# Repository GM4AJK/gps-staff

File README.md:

# GPS Survey Staff

A DIY RTK GNSS survey staff -- a handheld device for centimetre-level accurate position surveying.

## What is this?

The system consists of two identical handheld units: one set up as a fixed base station, the other carried by the surveyor as a rover. The two communicate wirelessly so the rover can compute corrected, centimetre-accurate positions in real time (RTK -- Real-Time Kinematic positioning).

It's designed to be self-contained and portable -- battery powered, with an onboard display, simple button/encoder controls, and onboard logging of survey data for later processing.

## Project status

Active development. PCB v1.0 ordered 2026-06-25. Firmware bring-up ongoing on Nucleo dev boards.

## Documentation

| Location | Contents |
|----------|----------|
| [`sdd/`](sdd/) | System design: architecture, unit specs, BLE protocols, UI screen specs |
| [`docs/arch/`](docs/arch/) | Firmware architecture: RTCM3, OTA protocol, SX1262 driver, SD card |
| [`docs/datasheets/`](docs/datasheets/) | Component datasheets and reference documents |
| [`hardware/rtk/`](hardware/rtk/) | PCB electronics design: KiCad files, BOM, design notes |

## License

MIT — see [LICENSE](LICENSE). This project is provided for educational and personal use without warranty of any kind. No liability is accepted for any use of these designs, including use in safety-critical or commercial applications. Use at your own risk.

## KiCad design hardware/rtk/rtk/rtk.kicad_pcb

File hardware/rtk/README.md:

# RTK PCB — Electronics Design

## PCB v1.0

- **Ordered:** 2026-06-25, JLCPCB. Tagged `PCB-v1.0` in git.
- **DigiKey BOM** ordered same date.
- **KiCad files:** `hardware/rtk/rtk/`
- **Component BOM:** [BOM.md](BOM.md)

### Board overview

| Property | Value |
|----------|-------|
| Layers | 4 (JLC04161H-7628 stackup) |
| Layer assignment | L1 top signal + components; L2 solid GND; L3 3.3V power plane; L4 bottom signal |
| RF traces | 50Ω microstrip on L1 (L2 GND reference); ~0.7mm trace width; JLCPCB controlled impedance |
| Design | Unified base + rover — single PCB, role selected by jumper at boot |
| Role-specific DNP | USB-C #1 (base: OTG FS) vs USB-C #2 + ULPI PHY (rover: OTG HS) |

### Unified PCB approach

Both units built from the same PCB. Mode selection:
- `PA0` (BASE_ROVER_MODE_SELECT): internal pull-up, link open = base, link to GND = rover
- Same STM32 firmware binary on both; mode gates peripheral init and code paths at runtime
- ESP32-S3 Zero firmware differs per role (base: WiFi NTRIP + BLE prov; rover: BLE GATT server)

---

## Schematic Connection Checklist

Consolidated list of every system wired on the schematic. Reference against the BOM and KiCad
to verify nothing is missed.

1. **ZED-F9P-05B** — UART1 (pins 42/43) → STM32 UART5 (nav + UBX config); UART2 (pins 26/27)
   → STM32 UART7 (PA8 RX ← F9P TXD2, PA15 TX → F9P RXD2) for RTCM input from LoRa;
   D_SEL (pin 47) → PE14 high (UART/I2C mode); RF_IN → GNSS SMA via 50Ω trace;
   1PPS → STM32 GPIO (log timestamping); power + decoupling.

2. **GNSS antenna (ANN-MB-00)** — SMA female through-hole; bias-T 3.3V LNA feed on RF line.

3. **LoRa (Core1262-LF / SX1262)** — dedicated SPI bus; BUSY checked before every transaction;
   DIO1/IRQ → STM32 GPIO; NRESET; separate SMA (433/434MHz).

4. **STM32F765VIT6** — UART (F9P + spare); 2× dedicated SPI (LoRa, IMU); SDMMC1 4-bit
   (PC8/D0, PC9/D1, PC10/D2, PC11/D3, PC12/CLK, PD2/CMD — fixed AF pins);
   I2C4 (PD12 SCL, PD13 SDA — display + IMU); USB OTG FS (PA11/PA12, base) or
   OTG HS + ULPI (rover); ADC (battery divider PA1); SWD.

5. **Power chain** — TPS63020 with D1 + C_SS soft-start on FB node; BQ24075 power-path
   (EN1/EN2/SYSOFF/nCE → STM32 GPIO outputs; nPGOOD/nCHG → STM32 GPIO inputs; TS → 10K to GND);
   LP103454-PCM-LD 2-wire battery connector (J3); 100K/100K battery voltage divider → PA1 ADC.

6. **USB-C (J1)** — single connector footprint, routed via USB3300 ULPI PHY (U8) to STM32
   OTG HS; CC1/CC2 5.1K pull-downs (R11/R12); USBLC6-2SC6 ESD (D2); USB3300 RST (PC1);
   24MHz TCXO (Y2); 12K RBIAS (R9); full decoupling.
   *(Base build: USB-C #2 + ULPI PHY fitted; USB-C #1 DNP. Both are HS-capable.)*

7. **IMU (LSM6DSOX/DSRX, U7)** — I2C4 (PD12/PD13); INT1 → PD14; INT2 → PD15.
   **Magnetometer (MMC5603NJ)** — sub-board via J11 (6-pin 0.1" header, I2C4 bus).

8. **SD card (J6)** — SDMMC1 4-bit bus (fixed AF pins above); card-detect → GPIO; well-decoupled VCC.

9. **STM32 backup domain (VBAT)** — wired directly to 3.3V rail; no coin cell.

10. **Config storage** — SD card file; no EEPROM fitted.

11. **OLED display (SSD1309)** — via J7 header; I2C4 bus (PD12 SCL, PD13 SDA); 0x3C/0x3D.
    On PCB v1.0. Driver bench-verified on F767ZI (task_display.c, ssd1309.c).

12. **Status LEDs** — LD3 (PD5, green) + LD4 (PD6, red): MCU open-drain + pull-ups R20/R21;
    LD1/LD2 hardwired to BQ24075 nPGOOD/nCHG.

13. **Mode-selection jumper** — PA0 GPIO input, internal pull-up; high = base, low = rover.

14. **BOOT0** — 2-pin header, 10K pull-down to GND; fitted = DFU bootloader.

15. **ESP32-S3 Zero (U5)** — spare STM32 UART; 3.3V power + decoupling; mode-select via
    PE2 (GP1) + PE3 (GP2/MODE_VALID). Base: WiFi NTRIP + BLE prov server.
    Rover: BLE GATT server to handheld.

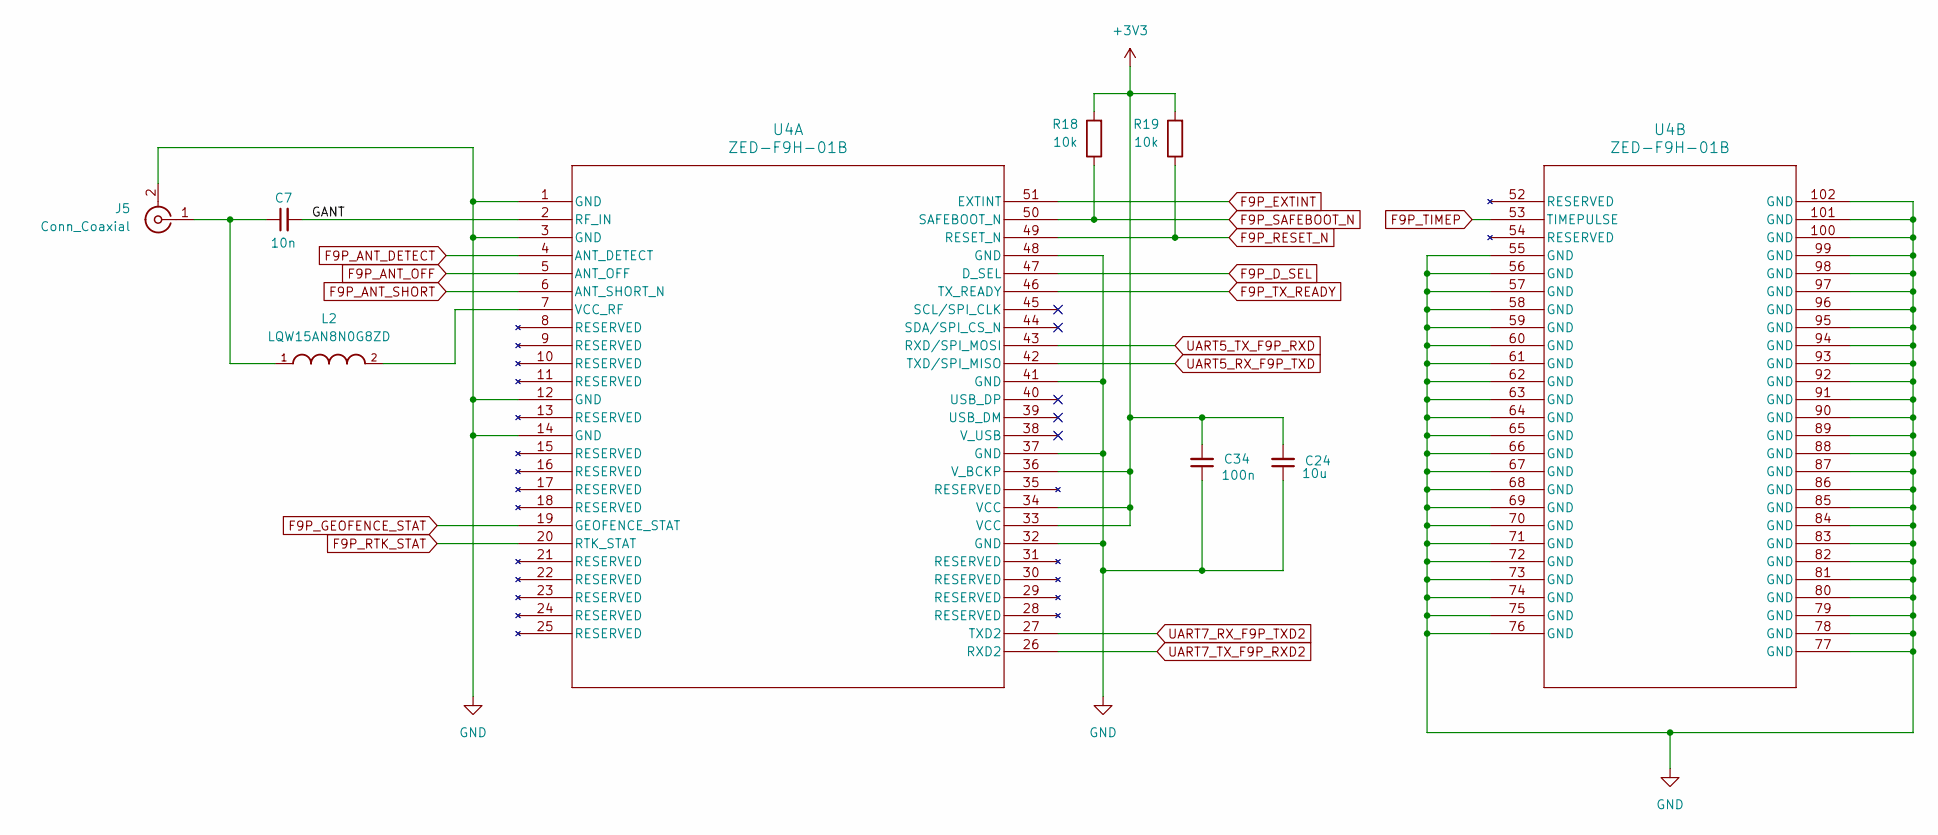
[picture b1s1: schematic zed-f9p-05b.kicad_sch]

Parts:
C7: 10n; C_0603_1608Metric_Pad1.08x0.95mm_HandSolder
C24: 10u; C_0805_2012Metric_Pad1.18x1.45mm_HandSolder
C34: 100n; C_0603_1608Metric_Pad1.08x0.95mm_HandSolder
J5: Conn_Coaxial; SMA_BAT_Wireless_BWSMA-KWE-Z001
L2: LQW15AN8N0G8ZD; INDC1006X60N
R18, R19: 10k; R_0805_2012Metric_Pad1.20x1.40mm_HandSolder
U4: ZED-F9H-01B; MOD54_ZED-F9H_UBL

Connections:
+3V3: C24.2, C34.2, R18.2, R19.2, U4.33 (VCC), U4.34 (VCC), U4.36 (V_BCKP); also elsewhere on the board
/ZED-F9P-05B/GANT: C7.2, U4.2 (RF_IN)
F9P_ANT_DETECT: U4.4 (ANT_DETECT); also elsewhere on the board
F9P_ANT_OFF: U4.5 (ANT_OFF); also elsewhere on the board
F9P_ANT_SHORT: U4.6 (ANT_SHORT_N); also elsewhere on the board
F9P_D_SEL: U4.47 (D_SEL); also elsewhere on the board
F9P_EXTINT: U4.51 (EXTINT); also elsewhere on the board
F9P_GEOFENCE_STAT: U4.19 (GEOFENCE_STAT); also elsewhere on the board
F9P_RESET_N: R19.1, U4.49 (RESET_N); also elsewhere on the board
F9P_RTK_STAT: U4.20 (RTK_STAT); also elsewhere on the board
F9P_SAFEBOOT_N: R18.1, U4.50 (SAFEBOOT_N); also elsewhere on the board
F9P_TIMEP: U4.53 (TIMEPULSE); also elsewhere on the board
F9P_TX_READY: U4.46 (TX_READY); also elsewhere on the board
GND: C24.1, C34.1, J5.2 (Ext), U4.1 (GND), U4.3 (GND), U4.12 (GND), U4.14 (GND), U4.32 (GND), U4.37 (GND), U4.41 (GND), U4.48 (GND), U4.55 (GND), U4.56 (GND), U4.57 (GND), U4.58 (GND), U4.59 (GND), U4.60 (GND), U4.61 (GND), U4.62 (GND), U4.63 (GND), U4.64 (GND), U4.65 (GND), U4.66 (GND), U4.67 (GND), U4.68 (GND), U4.69 (GND), U4.70 (GND), U4.71 (GND), U4.72 (GND), U4.73 (GND), U4.74 (GND), U4.75 (GND), U4.76 (GND), U4.77 (GND), U4.78 (GND), U4.79 (GND), U4.80 (GND), U4.81 (GND), U4.82 (GND), U4.83 (GND), U4.84 (GND), U4.85 (GND), U4.86 (GND), U4.87 (GND), U4.88 (GND), U4.89 (GND), U4.90 (GND), U4.91 (GND), U4.92 (GND), U4.93 (GND), U4.94 (GND), U4.95 (GND), U4.96 (GND), U4.97 (GND), U4.98 (GND), U4.99 (GND), U4.100 (GND), U4.101 (GND), U4.102 (GND); also elsewhere on the board
unnamed: C7.1, J5.1 (In), L2.1
unnamed: L2.2, U4.7 (VCC_RF)
UART5_RX_F9P_TXD: U4.42 (TXD/SPI_MISO); also elsewhere on the board
UART5_TX_F9P_RXD: U4.43 (RXD/SPI_MOSI); also elsewhere on the board
UART7_RX_F9P_TXD2: U4.27 (TXD2); also elsewhere on the board
UART7_TX_F9P_RXD2: U4.26 (RXD2); also elsewhere on the board

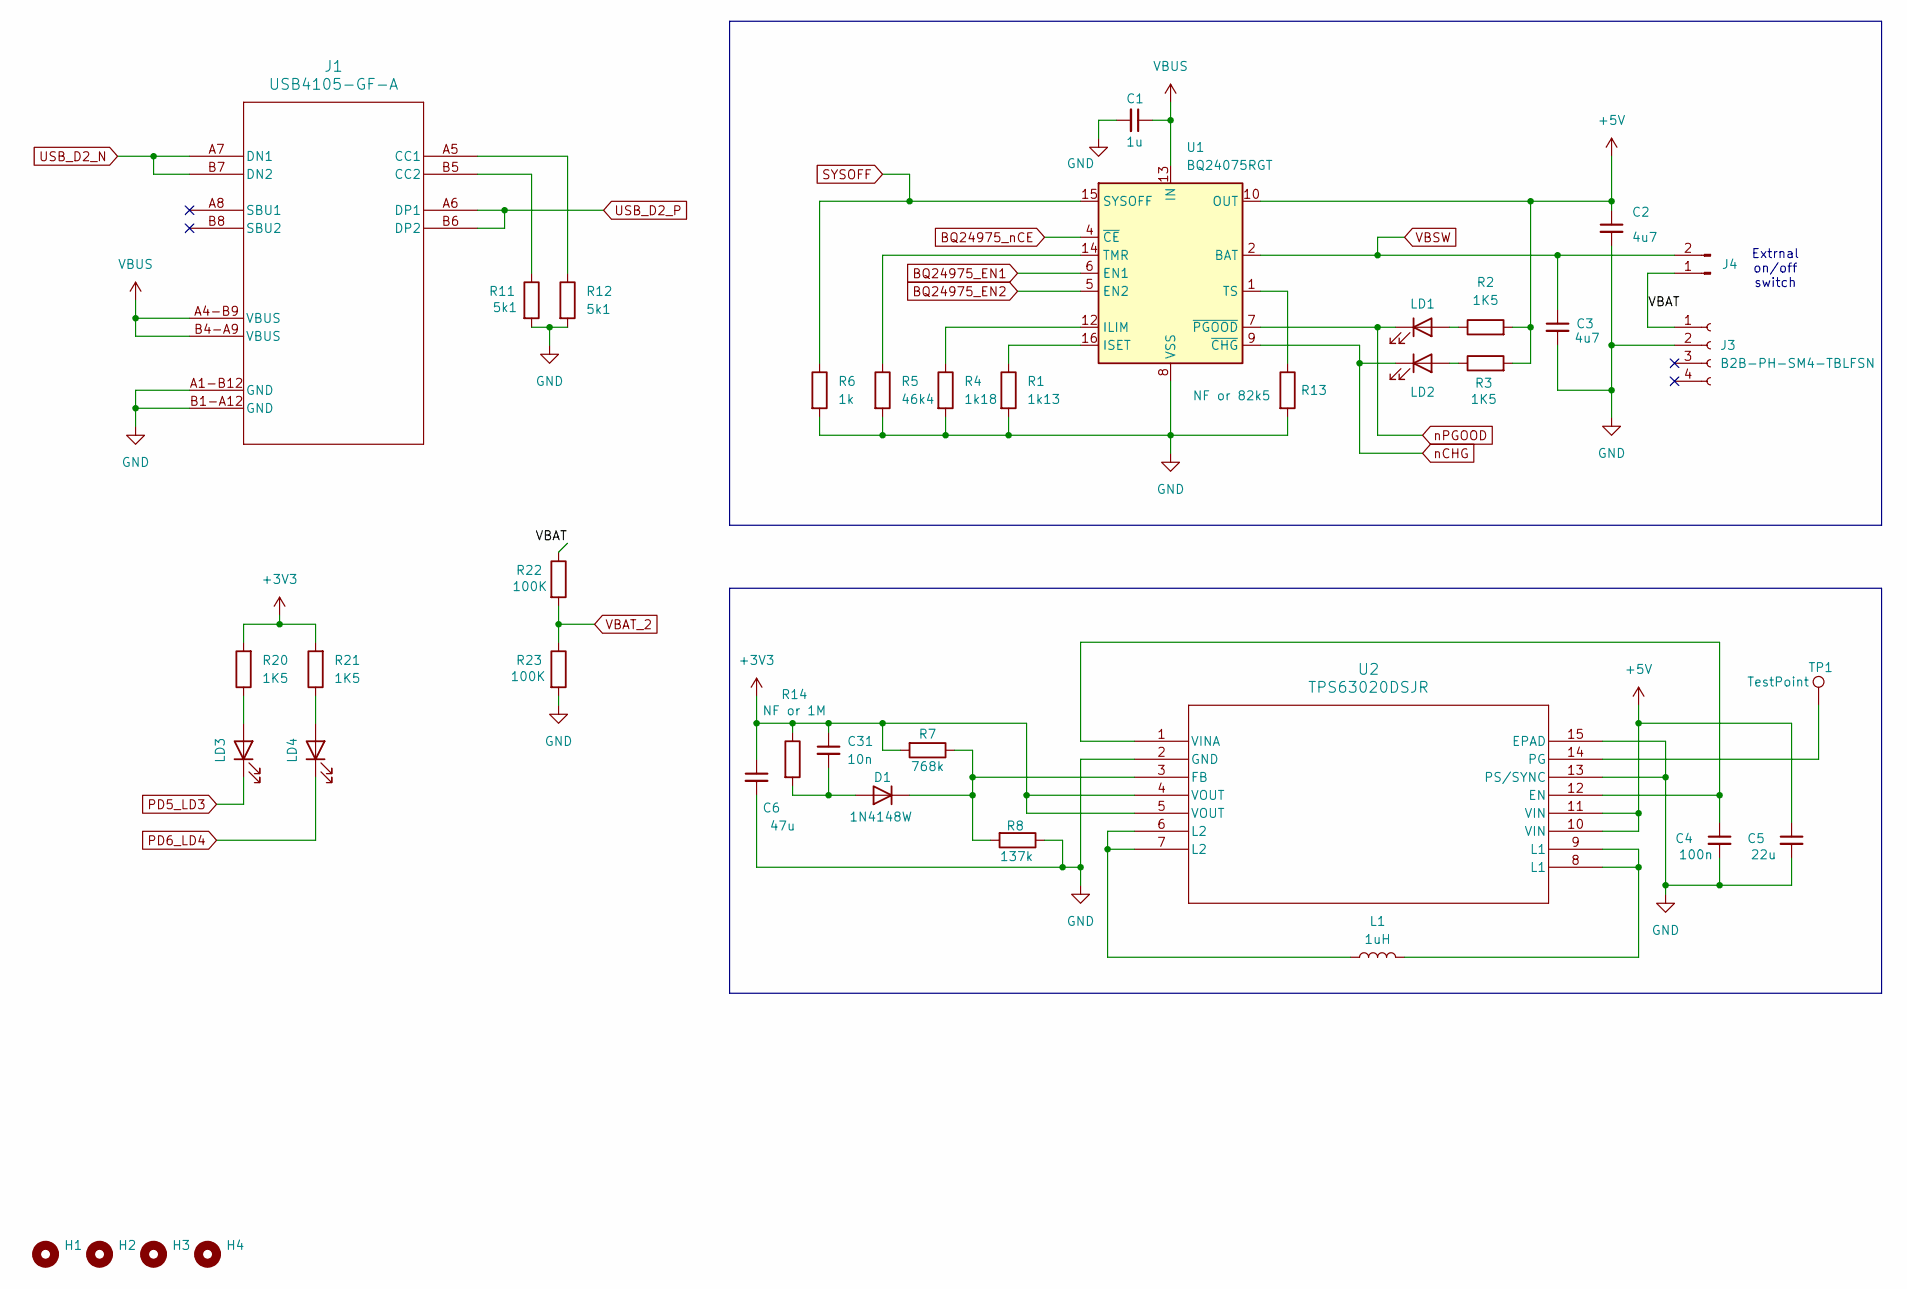
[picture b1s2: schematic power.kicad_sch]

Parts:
C1: 1u; C_0805_2012Metric_Pad1.18x1.45mm_HandSolder
C2, C3: 4u7; C_0805_2012Metric_Pad1.18x1.45mm_HandSolder
C4: 100n; C_0603_1608Metric_Pad1.08x0.95mm_HandSolder
C5: 22u; C_0603_1608Metric_Pad1.08x0.95mm_HandSolder
C6: 47u; C_0805_2012Metric_Pad1.18x1.45mm_HandSolder
C31: 10n; C_0805_2012Metric_Pad1.18x1.45mm_HandSolder
D1: 1N4148W; D_SOD-123
H1, H2, H3, H4: MountingHole; MountingHole_2.7mm
J1: USB4105-GF-A; USB4105_GCT
J3: B2B-PH-SM4-TBLFSN; CONN_B2B-PH-SM4-TBLFSN_JST
J4: Conn_01x02_Pin; PinHeader_1x02_P2.54mm_Vertical
L1: 1uH; IND_DFE2016_2X1P6_MUR
LD1, LD2, LD3, LD4: LED; LED_0805_2012Metric_Pad1.15x1.40mm_HandSolder
R1: 1k13; R_0805_2012Metric_Pad1.20x1.40mm_HandSolder
R2, R3, R20, R21: 1K5; R_0805_2012Metric_Pad1.20x1.40mm_HandSolder
R4: 1k18; R_0805_2012Metric_Pad1.20x1.40mm_HandSolder
R5: 46k4; R_0805_2012Metric_Pad1.20x1.40mm_HandSolder
R6: 1k; R_0805_2012Metric_Pad1.20x1.40mm_HandSolder
R7: 768k; R_0805_2012Metric_Pad1.20x1.40mm_HandSolder
R8: 137k; R_0805_2012Metric_Pad1.20x1.40mm_HandSolder
R11, R12: 5k1; R_0805_2012Metric_Pad1.20x1.40mm_HandSolder
R13: NF or 82k5; R_0805_2012Metric_Pad1.20x1.40mm_HandSolder
R14: NF or 1M; R_0805_2012Metric_Pad1.20x1.40mm_HandSolder
R22, R23: 100K; R_0805_2012Metric_Pad1.20x1.40mm_HandSolder
TP1: TestPoint; PinHeader_1x01_P2.54mm_Vertical
U1: BQ24075RGT; VQFN-16-1EP_3x3mm_P0.5mm_EP1.6x1.6mm
U2: TPS63020DSJR; DSJ14_2P85X1P58

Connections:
+3V3: C6.1, C31.1, R7.2, R14.1, R20.2, R21.2, U2.4 (VOUT), U2.5 (VOUT); also elsewhere on the board
+5V: C2.1, C5.1, R2.2, R3.2, U1.10 (OUT), U1.11 (OUT), U2.10 (VIN), U2.11 (VIN)
/Power/VBAT: J3.1, J4.1, R22.1
BQ24975_EN1: U1.6 (EN1); also elsewhere on the board
BQ24975_EN2: U1.5 (EN2); also elsewhere on the board
BQ24975_nCE: U1.4 (~CE); also elsewhere on the board
GND: C1.2, C2.2, C3.2, C4.2, C5.2, C6.2, J1.A1-B12 (GND), J1.B1-A12 (GND), J3.2, R1.2, R4.2, R5.2, R6.2, R8.1, R11.2, R12.2, R13.2, R23.2, U1.8 (VSS), U1.17 (VSS), U2.2 (GND), U2.13 (PS/SYNC), U2.15 (EPAD); also elsewhere on the board
unnamed: C31.2, D1.2 (A), R14.2
unnamed: D1.1 (K), R7.1, R8.2, U2.3 (FB)
unnamed: J1.A5 (CC1), R12.1
unnamed: J1.B5 (CC2), R11.1
unnamed: L1.1, U2.6 (L2), U2.7 (L2)
unnamed: L1.2, U2.8 (L1), U2.9 (L1)
unnamed: LD1.2 (A), R2.1
unnamed: LD2.2 (A), R3.1
unnamed: LD3.2 (A), R20.1
unnamed: LD4.2 (A), R21.1
unnamed: R4.1, U1.12 (ILIM)
unnamed: R1.1, U1.16 (ISET)
unnamed: R5.1, U1.14 (TMR)
unnamed: R13.1, U1.1 (TS)
unnamed: C4.1, U2.1 (VINA), U2.12 (EN)
unnamed: TP1.1 (1_1), U2.14 (PG)
PD5_LD3: LD3.1 (K); also elsewhere on the board
PD6_LD4: LD4.1 (K); also elsewhere on the board
SYSOFF: R6.1, U1.15 (SYSOFF); also elsewhere on the board
USB_D2_N: J1.A7 (DN1), J1.B7 (DN2); also elsewhere on the board
USB_D2_P: J1.A6 (DP1), J1.B6 (DP2); also elsewhere on the board
VBAT_2: R22.2, R23.1; also elsewhere on the board
VBSW: C3.1, J4.2, U1.2 (BAT), U1.3 (BAT)
VBUS: C1.1, J1.A4-B9 (VBUS), J1.B4-A9 (VBUS), U1.13 (IN); also elsewhere on the board
nCHG: LD2.1 (K), U1.9 (~CHG); also elsewhere on the board
nPGOOD: LD1.1 (K), U1.7 (~PGOOD); also elsewhere on the board

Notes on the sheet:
Extrnal on/off switch

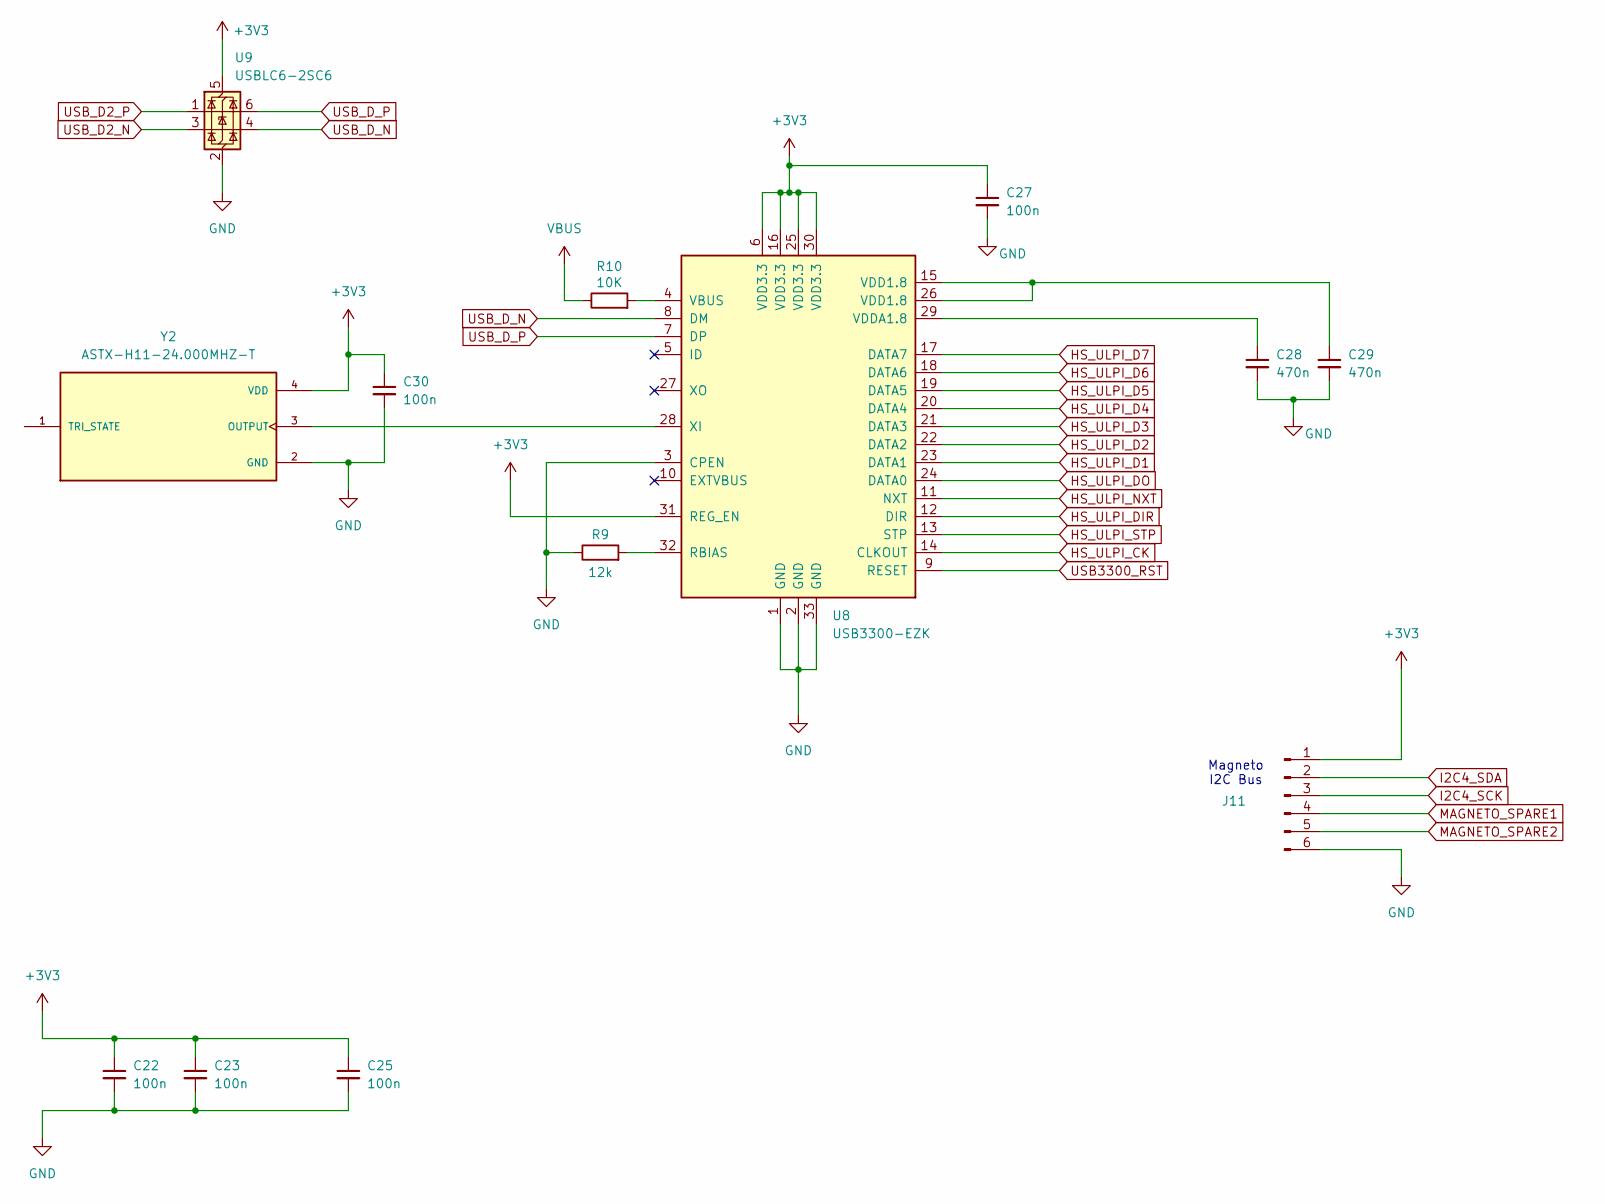
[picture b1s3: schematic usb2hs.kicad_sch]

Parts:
C22, C23, C25, C27, C30: 100n; C_0805_2012Metric_Pad1.18x1.45mm_HandSolder
C28, C29: 470n; C_0805_2012Metric_Pad1.18x1.45mm_HandSolder
J11: Conn_01x06_Pin; PinHeader_1x06_P2.54mm_Vertical
R9: 12k; R_0805_2012Metric_Pad1.20x1.40mm_HandSolder
R10: 10K; R_0805_2012Metric_Pad1.20x1.40mm_HandSolder
U8: USB3300-EZK; QFN-32-1EP_5x5mm_P0.5mm_EP3.45x3.45mm
U9: USBLC6-2SC6; SOT-23-6
Y2: ASTX-H11-24.000MHZ-T; XTAL_ASTX-H11-16.000MHZ-T; PARTREV 05.13.15

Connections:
+3V3: C22.1, C23.1, C25.1, C27.1, C30.1, J11.1, U8.6 (VDD3.3), U8.16 (VDD3.3), U8.25 (VDD3.3), U8.30 (VDD3.3), U8.31 (REG_EN), U9.5 (VBUS), Y2.4 (VDD); also elsewhere on the board
GND: C22.2, C23.2, C25.2, C27.2, C28.2, C29.2, C30.2, J11.6, R9.1, U8.1 (GND), U8.2 (GND), U8.3 (CPEN), U8.33 (GND), U9.2 (GND), Y2.2 (GND); also elsewhere on the board
HS_ULPI_CK: U8.14 (CLKOUT); also elsewhere on the board
HS_ULPI_D1: U8.23 (DATA1); also elsewhere on the board
HS_ULPI_D2: U8.22 (DATA2); also elsewhere on the board
HS_ULPI_D3: U8.21 (DATA3); also elsewhere on the board
HS_ULPI_D4: U8.20 (DATA4); also elsewhere on the board
HS_ULPI_D5: U8.19 (DATA5); also elsewhere on the board
HS_ULPI_D6: U8.18 (DATA6); also elsewhere on the board
HS_ULPI_D7: U8.17 (DATA7); also elsewhere on the board
HS_ULPI_DIR: U8.12 (DIR); also elsewhere on the board
HS_ULPI_DO: U8.24 (DATA0); also elsewhere on the board
HS_ULPI_NXT: U8.11 (NXT); also elsewhere on the board
HS_ULPI_STP: U8.13 (STP); also elsewhere on the board
I2C4_SCK: J11.3; also elsewhere on the board
I2C4_SDA: J11.2; also elsewhere on the board
MAGNETO_SPARE1: J11.4; also elsewhere on the board
MAGNETO_SPARE2: J11.5; also elsewhere on the board
unnamed: C29.1, U8.15 (VDD1.8), U8.26 (VDD1.8)
unnamed: R9.2, U8.32 (RBIAS)
unnamed: R10.2, U8.4 (VBUS)
unnamed: C28.1, U8.29 (VDDA1.8)
unnamed: U8.28 (XI), Y2.3 (OUTPUT)
USB3300_RST: U8.9 (RESET); also elsewhere on the board
USB_D2_N: U9.3 (I/O2); also elsewhere on the board
USB_D2_P: U9.1 (I/O1); also elsewhere on the board
USB_D_N: U8.8 (DM), U9.4 (I/O2)
USB_D_P: U8.7 (DP), U9.6 (I/O1)
VBUS: R10.1; also elsewhere on the board

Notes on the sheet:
Magneto I2C Bus

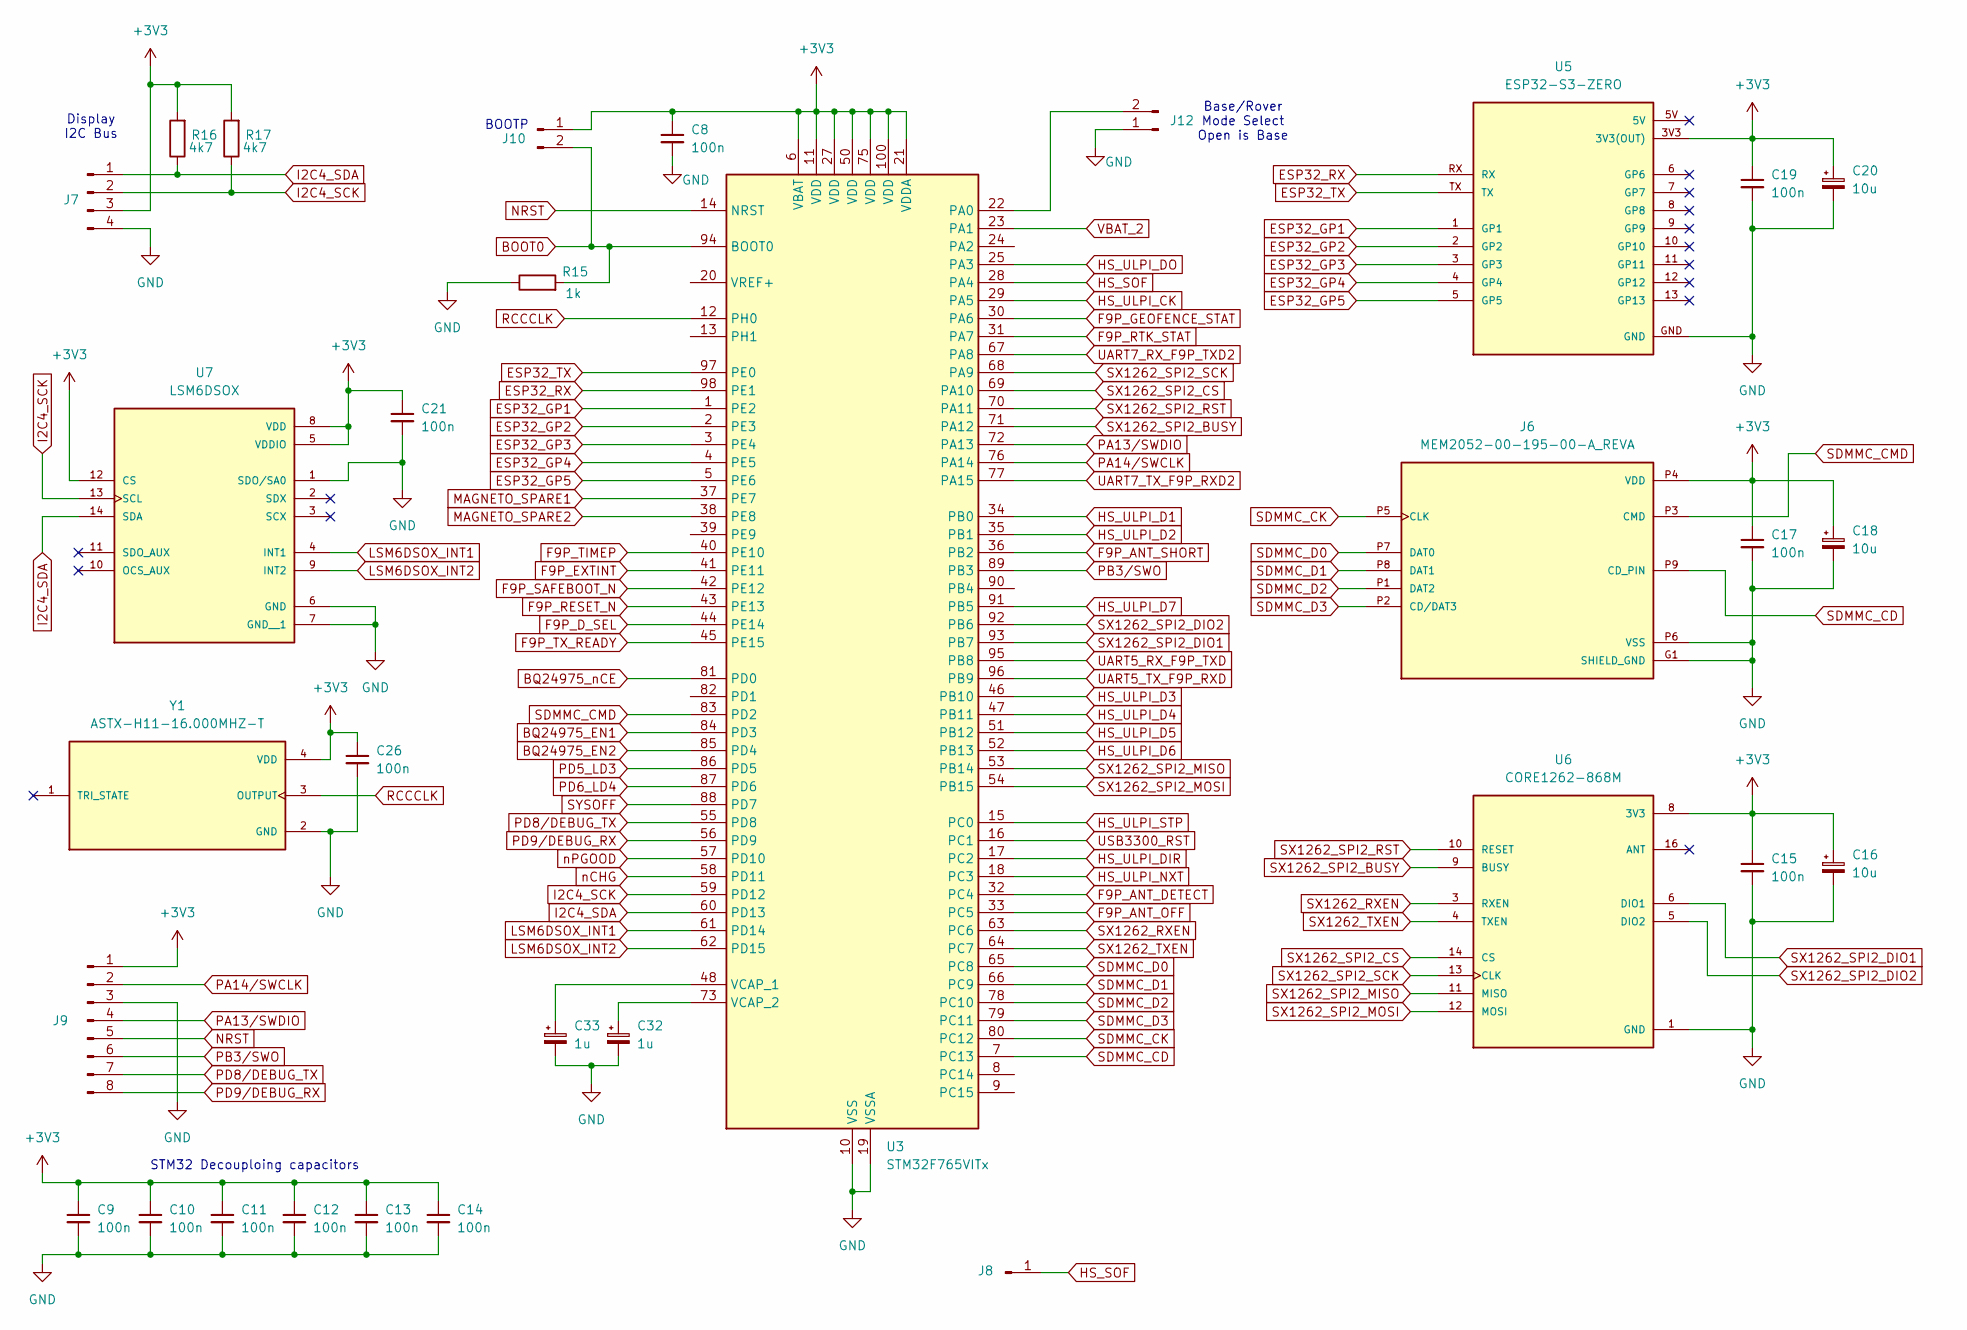
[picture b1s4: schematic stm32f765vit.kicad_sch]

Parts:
C8, C9, C10, C11, C12, C13, C14, C15, C17, C19, C21, C26: 100n; C_0805_2012Metric_Pad1.18x1.45mm_HandSolder
C16, C18, C20: 10u; C_0805_2012Metric_Pad1.18x1.45mm_HandSolder
C32, C33: 1u; C_0805_2012Metric_Pad1.18x1.45mm_HandSolder
J6: MEM2052-00-195-00-A_REVA; GCT_MEM2052-00-195-00-A_REVA; PARTREV A
J7: Conn_01x04_Pin; PinHeader_1x04_P2.54mm_Vertical
J8: Conn_01x01_Pin; PinHeader_1x01_P2.54mm_Vertical
J9: Conn_01x08_Pin; PinHeader_1x08_P2.54mm_Vertical
J10, J12: Conn_01x02_Pin; PinHeader_1x02_P2.54mm_Vertical
R15: 1k; R_0805_2012Metric_Pad1.20x1.40mm_HandSolder
R16, R17: 4k7; R_0805_2012Metric_Pad1.20x1.40mm_HandSolder
U3: STM32F765VITx; LQFP-100_14x14mm_P0.5mm
U5: ESP32-S3-ZERO; MODULE_ESP32-S3-ZERO; PARTREV NA
U6: CORE1262-868M; XCVR_CORE1262-868M; PARTREV N/A
U7: LSM6DSOX; PQFN50P250X300X86-14N; PARTREV 3.0
Y1: ASTX-H11-16.000MHZ-T; XTAL_ASTX-H11-16.000MHZ-T; PARTREV 05.13.15

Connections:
+3V3: C8.1, C9.1, C10.1, C11.1, C12.1, C13.1, C14.1, C15.1, C16.1, C17.1, C18.1, C19.1, C20.1, C21.1, C26.1, J6.P4 (VDD), J7.3, J9.1, J10.1, R16.2, R17.2, U3.6 (VBAT), U3.11 (VDD), U3.21 (VDDA), U3.27 (VDD), U3.50 (VDD), U3.75 (VDD), U3.100 (VDD), U5.3V3 (3V3(OUT)), U6.8 (3V3), U7.5 (VDDIO), U7.8 (VDD), U7.12 (CS), Y1.4 (VDD); also elsewhere on the board
BOOT0: J10.2, R15.2, U3.94 (BOOT0)
BQ24975_EN1: U3.84 (PD3); also elsewhere on the board
BQ24975_EN2: U3.85 (PD4); also elsewhere on the board
BQ24975_nCE: U3.81 (PD0); also elsewhere on the board
ESP32_GP1: U3.1 (PE2), U5.1 (GP1)
ESP32_GP2: U3.2 (PE3), U5.2 (GP2)
ESP32_GP3: U3.3 (PE4), U5.3 (GP3)
ESP32_GP4: U3.4 (PE5), U5.4 (GP4)
ESP32_GP5: U3.5 (PE6), U5.5 (GP5)
ESP32_RX: U3.98 (PE1), U5.RX
ESP32_TX: U3.97 (PE0), U5.TX
F9P_ANT_DETECT: U3.32 (PC4); also elsewhere on the board
F9P_ANT_OFF: U3.33 (PC5); also elsewhere on the board
F9P_ANT_SHORT: U3.36 (PB2); also elsewhere on the board
F9P_D_SEL: U3.44 (PE14); also elsewhere on the board
F9P_EXTINT: U3.41 (PE11); also elsewhere on the board
F9P_GEOFENCE_STAT: U3.30 (PA6); also elsewhere on the board
F9P_RESET_N: U3.43 (PE13); also elsewhere on the board
F9P_RTK_STAT: U3.31 (PA7); also elsewhere on the board
F9P_SAFEBOOT_N: U3.42 (PE12); also elsewhere on the board
F9P_TIMEP: U3.40 (PE10); also elsewhere on the board
F9P_TX_READY: U3.45 (PE15); also elsewhere on the board
GND: C8.2, C9.2, C10.2, C11.2, C12.2, C13.2, C14.2, C15.2, C16.2, C17.2, C18.2, C19.2, C20.2, C21.2, C26.2, C32.2, C33.2, J6.G1 (SHIELD_GND), J6.G2 (SHIELD_GND), J6.G3 (SHIELD_GND), J6.G4 (SHIELD_GND), J6.P6 (VSS), J7.4, J9.3, J12.1, R15.1, U3.10 (VSS), U3.19 (VSSA), U3.26 (VSS), U3.49 (VSS), U3.74 (VSS), U3.99 (VSS), U5.GND, U6.1 (GND), U6.2 (GND), U6.7 (GND), U6.15 (GND), U7.1 (SDO/SA0), U7.6 (GND), U7.7 (GND__1), Y1.2 (GND); also elsewhere on the board
HS_SOF: J8.1 (Pin_1_1), U3.28 (PA4)
HS_ULPI_CK: U3.29 (PA5); also elsewhere on the board
HS_ULPI_D1: U3.34 (PB0); also elsewhere on the board
HS_ULPI_D2: U3.35 (PB1); also elsewhere on the board
HS_ULPI_D3: U3.46 (PB10); also elsewhere on the board
HS_ULPI_D4: U3.47 (PB11); also elsewhere on the board
HS_ULPI_D5: U3.51 (PB12); also elsewhere on the board
HS_ULPI_D6: U3.52 (PB13); also elsewhere on the board
HS_ULPI_D7: U3.91 (PB5); also elsewhere on the board
HS_ULPI_DIR: U3.17 (PC2); also elsewhere on the board
HS_ULPI_DO: U3.25 (PA3); also elsewhere on the board
HS_ULPI_NXT: U3.18 (PC3); also elsewhere on the board
HS_ULPI_STP: U3.15 (PC0); also elsewhere on the board
I2C4_SCK: J7.2, R17.1, U3.59 (PD12), U7.13 (SCL); also elsewhere on the board
I2C4_SDA: J7.1, R16.1, U3.60 (PD13), U7.14 (SDA); also elsewhere on the board
LSM6DSOX_INT1: U3.61 (PD14), U7.4 (INT1)
LSM6DSOX_INT2: U3.62 (PD15), U7.9 (INT2)
MAGNETO_SPARE1: U3.37 (PE7); also elsewhere on the board
MAGNETO_SPARE2: U3.38 (PE8); also elsewhere on the board
NRST: J9.5, U3.14 (NRST)
unnamed: J12.2, U3.22 (PA0)
unnamed: C33.1, U3.48 (VCAP_1)
unnamed: C32.1, U3.73 (VCAP_2)
PA13/SWDIO: J9.4, U3.72 (PA13)
PA14/SWCLK: J9.2, U3.76 (PA14)
PB3/SWO: J9.6, U3.89 (PB3)
PD5_LD3: U3.86 (PD5); also elsewhere on the board
PD6_LD4: U3.87 (PD6); also elsewhere on the board
PD8/DEBUG_TX: J9.7, U3.55 (PD8)
PD9/DEBUG_RX: J9.8, U3.56 (PD9)
RCCCLK: U3.12 (PH0), Y1.3 (OUTPUT)
SDMMC_CD: J6.P9 (CD_PIN), U3.7 (PC13)
SDMMC_CK: J6.P5 (CLK), U3.80 (PC12)
SDMMC_CMD: J6.P3 (CMD), U3.83 (PD2)
SDMMC_D0: J6.P7 (DAT0), U3.65 (PC8)
SDMMC_D1: J6.P8 (DAT1), U3.66 (PC9)
SDMMC_D2: J6.P1 (DAT2), U3.78 (PC10)
SDMMC_D3: J6.P2 (CD/DAT3), U3.79 (PC11)
SX1262_RXEN: U3.63 (PC6), U6.3 (RXEN)
SX1262_SPI2_BUSY: U3.71 (PA12), U6.9 (BUSY)
SX1262_SPI2_CS: U3.69 (PA10), U6.14 (CS)
SX1262_SPI2_DIO1: U3.93 (PB7), U6.6 (DIO1)
SX1262_SPI2_DIO2: U3.92 (PB6), U6.5 (DIO2)
SX1262_SPI2_MISO: U3.53 (PB14), U6.11 (MISO)
SX1262_SPI2_MOSI: U3.54 (PB15), U6.12 (MOSI)
SX1262_SPI2_RST: U3.70 (PA11), U6.10 (RESET)
SX1262_SPI2_SCK: U3.68 (PA9), U6.13 (CLK)
SX1262_TXEN: U3.64 (PC7), U6.4 (TXEN)
SYSOFF: U3.88 (PD7); also elsewhere on the board
UART5_RX_F9P_TXD: U3.95 (PB8); also elsewhere on the board
UART5_TX_F9P_RXD: U3.96 (PB9); also elsewhere on the board
UART7_RX_F9P_TXD2: U3.67 (PA8); also elsewhere on the board
UART7_TX_F9P_RXD2: U3.77 (PA15); also elsewhere on the board
USB3300_RST: U3.16 (PC1); also elsewhere on the board
VBAT_2: U3.23 (PA1); also elsewhere on the board
nCHG: U3.58 (PD11); also elsewhere on the board
nPGOOD: U3.57 (PD10); also elsewhere on the board

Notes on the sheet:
Base/Rover Mode Select Open is Base
STM32 Decouploing capacitors
Display I2C Bus
BOOTP

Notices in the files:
hardware/rtk/rtk/rtk.kicad_pcb:
(c)2026
